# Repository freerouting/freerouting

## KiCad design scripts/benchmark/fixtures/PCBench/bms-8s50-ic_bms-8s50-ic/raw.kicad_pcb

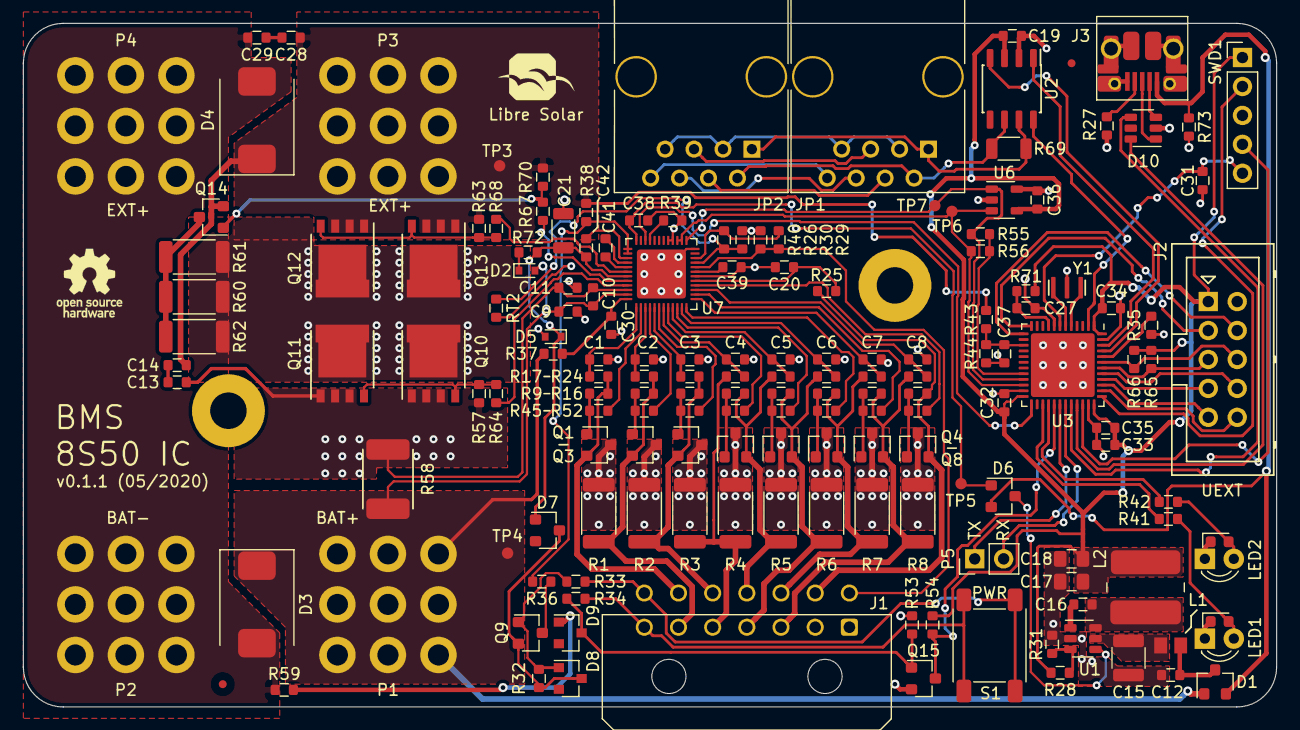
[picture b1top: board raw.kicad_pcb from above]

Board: 2 copper layers, 110.0 x 60.0 mm, 166 parts (0 on the bottom side), 125 nets.

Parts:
C1, C2, C3, C4, C5, C6, C7, C8, C20: 47n; C_0603_1608
C9, C11, C12, C39: 1u; C_0603_1608
C10: 10n; C_0603_1608
C13, C14, C16, C19, C27, C28, C29, C31, C32, C33, C34, C36, C38: 100n; C_0603_1608
C15: 4.7u; C_1210_3225
C17, C18: 10u; C_0805_2012
C21: 4.7u; C_1206_3216
C30: 470n; C_0603_1608
C35: 4.7u; C_0603_1608
C37, C41, C42: 4.7n; C_0603_1608
D1, D6, D7: BAV70; SOT-23
D2, D5: PMEG6002; D_SOD-523
D3, D4: SMCJ36A; D_SMC
D8, D9: 12V; D_SOT-23_ANK
D10: USBLC6-2SC6; SOT-23-6
H1, H2: MountingHole; MountingHole_3.2mm_M3_Pad
J1: Conn_01x10; Molex_Micro-Fit_3.0_43045-1400_2x07_P3.00mm_Horizontal
J2: UEXT; Box_Header_2x05x2.54mm_Straight
J3: USB_B_Micro; USB_Micro-B_10103594-0001LF
JP1, JP2: RJ45_NS; RJ45_8P8C
L1: 4.7uH; L_0805_2012Metric
L2: 47uH; Bourns_SRN6045TA
LED1, LED2: LED; LED_0603_D3.0mm
LOGO1: OPEN_HARDWARE; OSHW-Logo_5.7x6mm_SilkScreen
LOGO2: LIBRE_SOLAR; LIBRESOLAR_LOGO
P1, P2, P3, P4: CONN_01X01; Wuerth_WP-THRBU_74650195
P5: CONN_01X02; PinHeader_1x02_P2.54mm_Vertical
Q1, Q2, Q3, Q9: NDS0605; SOT-23
Q4, Q5, Q6, Q7, Q8, Q14, Q15: BSS138; SOT-23
Q10, Q11, Q12, Q13: BSC016N06NS; 5X6_MOSFET
R1, R2, R3, R4, R5, R6, R7, R8: 33; R_2010_5025
R9, R10, R11, R12, R13, R14, R15, R16, R27, R43, R73: 330k; R_0603_1608
R17, R18, R19, R20, R21, R22, R23, R24, R25, R36, R38, R41, R42, R54: 1k; R_0603_1608
R26, R30, R33, R34, R45, R46, R47, R48, R49, R50, R51, R52: 10k; R_0603_1608
R28: 50.5k; R_0603_1608
R29, R31, R40, R44: 22k; R_0603_1608
R32, R35, R53, R57, R63, R70: 1M; R_0603_1608
R37, R59, R64, R67, R68, R71: 100; R_0603_1608
R39, R55, R56, R65, R66: 2.2k; R_0603_1608
R58: 1m; R_Shunt_2512
R60, R61, R62: 330; R_2010_5025
R69: 120; R_1206_3216
R72: 4R7; R_0603_1608
RT2: 10k; R_0603_1608
S1: SW_PUSH; SW_SPST_6mm
SWD1: ST_Nucleo_SWD_5p; PinHeader_1x05_P2.54mm_Vertical
TP3: Ext+; TestPoint_1mm_pad
TP4: Bat+; TestPoint_1mm_pad
TP5: Regout; TestPoint_1mm_pad
TP6: SDA; TestPoint_1mm_pad
TP7: SCL; TestPoint_1mm_pad
U1: TPS560430X; SOT-23-6
U2: TCAN334; SOIC-8_3.9x4.9mm_Pitch1.27mm
U3: STM32F072CBU6; QFN-48-1EP_7x7mm_P0.5mm_EP5.6x5.6mm
U6: 24AA32; SOT-23-5
U7: ISL94202; QFN-48-1EP_6x6mm_P0.4mm_EP4.3x4.3mm
Y1: 8MHz; Resonator_Murata_CSTNE

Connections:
+3V3: C17.1, C18.1, C19.1, C32.1, C33.1, C34.1, C35.1, C36.1, J2.1, L2.2, R28.1, R54.2, R65.2, R66.2, R71.2, SWD1.1, U2.3, U3.1, U3.24, U3.36, U3.48, U6.4
+5V: D1.2, D6.2, J3.1, R73.1
/BAT+: C9.1, C10.1, D1.1, D2.2, D3.1, P1.1, R37.1, R58.2, TP4.1, U7.47
/BAT-: C29.2, D3.2, D4.2, P2.1, P4.1, R59.1
/CAN_V+: JP1.8, JP2.8
/EXT+: C14.2, C28.1, D4.1, P3.1, Q12.S, Q13.S, Q14.2, R38.1, R43.1, R63.1, R70.1, TP3.1
/ISL94202/ALERT: U3.25, U7.34
/ISL94202/BTN_1: J1.14, R33.1, S1.2
/ISL94202/BTN_2: J1.7, R34.2, S1.1
/ISL94202/BTN_SIGNAL: Q15.3, R54.1, U3.29
/ISL94202/CB1: R52.1, U7.16
/ISL94202/CB2: R51.1, U7.14
/ISL94202/CB3: R50.1, U7.12
/ISL94202/CB4: R49.1, U7.10
/ISL94202/CB5: R48.1, U7.8
/ISL94202/CB6: R47.1, U7.6
/ISL94202/CB7: R46.1, U7.4
/ISL94202/CB8: R45.1, U7.2
/ISL94202/CELL1+: J1.3, Q7.2, R8.2, R15.1, R24.2
/ISL94202/CELL1-: J1.9, Q8.2, R16.1, R25.2
/ISL94202/CELL2+: J1.10, Q6.2, R7.2, R14.1, R23.2
/ISL94202/CELL3+: J1.4, Q5.2, R6.2, R13.1, R22.2
/ISL94202/CELL4+: J1.11, Q4.2, R5.2, R12.1, R21.2
/ISL94202/CELL5+: J1.5, R3.1, R4.2, R20.2
/ISL94202/CELL6+: J1.12, Q3.2, R2.1, R11.2, R19.2
/ISL94202/CELL7+: J1.6, Q2.2, R1.1, R10.2, R18.2
/ISL94202/CELL8+: J1.13, Q1.2, R9.2, R17.2
/ISL94202/CFET: R64.2, U7.45
/ISL94202/CHG+: D5.2, Q10.D, Q11.D, Q12.D, Q13.D, R60.2, R61.2, R62.2
/ISL94202/CHMON: R36.1, R38.2, U7.37, U7.38
/ISL94202/CSI2: C10.2, C11.1, C13.1, Q10.S, Q11.S, R57.2, R58.1, U7.46
/ISL94202/DFET: R68.1, U7.42
/ISL94202/NTC_BAT: J1.8, R29.1, R30.2, U7.20
/ISL94202/PCFET: R67.2, U7.44
/ISL94202/RGO: C38.1, D6.1, TP5.1, U7.36
/ISL94202/TEMPO: R29.2, R40.2, U7.22
/ISL94202/VC0: C20.1, R25.1, U7.17
/ISL94202/VC1: C8.1, R24.1, U7.15
/ISL94202/VC2: C7.1, R23.1, U7.13
/ISL94202/VC3: C6.1, R22.1, U7.11
/ISL94202/VC4: C5.1, R21.1, U7.9
/ISL94202/VC5: C4.1, R20.1, U7.7
/ISL94202/VC6: C3.1, R19.1, U7.5
/ISL94202/VC7: C2.1, R18.1, U7.3
/ISL94202/VC8: C1.1, R17.1, U7.1
/ISL94202/VDD: C21.1, C42.1, D5.1, D7.1, R72.1, U7.43
/ISL94202/XT2: R26.2, R40.1, RT2.1, U7.21
/MCU/BOOT0: R35.2, U3.44
/MCU/CAN_H: JP1.1, JP2.1, R69.1, U2.7
/MCU/CAN_L: JP1.2, JP2.2, R69.2, U2.6
/MCU/CAN_RX: U2.4, U3.45
/MCU/CAN_STB: U2.8, U3.2
/MCU/CAN_TX: U2.1, U3.46
/MCU/I2C1_SCL: J2.5, R65.1, U3.42
/MCU/I2C1_SDA: J2.6, R66.1, U3.43
/MCU/I2C2_PULLUP: R55.2, R56.2, U3.20
/MCU/I2C2_SCL: R55.1, TP7.1, U3.21, U6.1, U7.25
/MCU/I2C2_SDA: R56.1, TP6.1, U3.22, U6.3, U7.26, U7.27
/MCU/LED1: R41.2, U3.27
/MCU/LED2: R42.2, U3.28
/MCU/SPI1_MISO: J2.7, U3.40
/MCU/SPI1_MOSI: J2.8, U3.41
/MCU/SPI1_SCK: J2.9, U3.39
/MCU/SSEL: J2.10, U3.38
/MCU/SWCLK: SWD1.2, U3.37
/MCU/SWDIO: SWD1.4, U3.34
/MCU/USART1_RX: P5.2, U3.31
/MCU/USART1_TX: P5.1, U3.30
/MCU/USART2_RX: J2.4, U3.13
/MCU/USART2_TX: J2.3, U3.12
/MCU/USB_D+: D10.1, J3.3
/MCU/USB_D-: D10.3, J3.2
/MCU/USB_DM: D10.4, U3.32
/MCU/USB_DP: D10.6, U3.33
/MCU/~RESET: C31.1, SWD1.5, U3.7
/Power Supply/EN: D6.3, U1.4
/Power Supply/FB: R28.2, R31.1, U1.3
/Power Supply/SW: C16.2, L2.1, U1.6
/Power Supply/VIN: C15.1, L1.2, U1.5
/V_EXT: C37.1, R43.2, R44.1, U3.15
GND: C1.2, C2.2, C3.2, C4.2, C5.2, C6.2, C7.2, C8.2, C9.2, C11.2, C12.2, C15.2, C17.2, C18.2, C19.2, C20.2, C21.2, C27.2, C30.2, C31.2, C32.2, C33.2, C34.2, C35.2, C36.2, C37.2, C38.2, C39.2, D9.2, D10.2, J1.1, J1.2, J2.2, J3.5, J3.6, JP1.3, JP1.7, JP2.3, JP2.7, LED1.1, LED2.1, Q15.2, R26.1, R27.2, R30.1, R31.2, R35.1, R39.2, R44.2, R53.1, R59.2, R73.2, RT2.2, SWD1.3, U1.2, U2.2, U3.8, U3.23, U3.35, U3.47, U3.49, U6.2, U6.5, U7.18, U7.24, U7.28, U7.29, U7.49, Y1.2
unnamed: C12.1, D1.3, L1.1
unnamed: C13.2, C14.1
unnamed: C16.1, U1.1
unnamed: C27.1, R71.1, U3.9
unnamed: C28.2, C29.1
unnamed: C30.1, R37.2, U7.48
unnamed: C39.1, U7.19
unnamed: C41.1, U7.41
unnamed: C41.2, U7.40
unnamed: C42.2, U7.39
unnamed: D2.1, R72.2
unnamed: D7.3, D8.1, Q9.2, R32.2
unnamed: D8.2, Q9.1, R32.1, R33.2
unnamed: D9.1, Q15.1, R34.1, R53.2
unnamed: J3.4, R27.1
unnamed: JP1.4, JP2.4
unnamed: JP1.5, JP2.5
unnamed: JP1.6, JP2.6
unnamed: LED1.2, R41.1
unnamed: LED2.2, R42.1
unnamed: Q1.1, R9.1, R45.2
unnamed: Q1.3, R1.2
unnamed: Q2.1, R10.1, R46.2
unnamed: Q2.3, R2.2
unnamed: Q3.1, R11.1, R47.2
unnamed: Q3.3, R3.2
unnamed: Q4.1, R12.2, R48.2
unnamed: Q4.3, R4.1
unnamed: Q5.1, R13.2, R49.2
unnamed: Q5.3, R5.1
unnamed: Q6.1, R14.2, R50.2
unnamed: Q6.3, R6.1
unnamed: Q7.1, R15.2, R51.2
unnamed: Q7.3, R7.1
unnamed: Q8.1, R16.2, R52.2
unnamed: Q8.3, R8.1
unnamed: Q9.3, R36.2
unnamed: Q10.G, Q11.G, R57.1, R64.1
unnamed: Q12.G, Q13.G, R63.2, R68.2
unnamed: Q14.1, R67.1, R70.2
unnamed: Q14.3, R60.1, R61.1, R62.1
unnamed: R39.1, U7.33
unnamed: U3.5, Y1.3
unnamed: U3.6, Y1.1

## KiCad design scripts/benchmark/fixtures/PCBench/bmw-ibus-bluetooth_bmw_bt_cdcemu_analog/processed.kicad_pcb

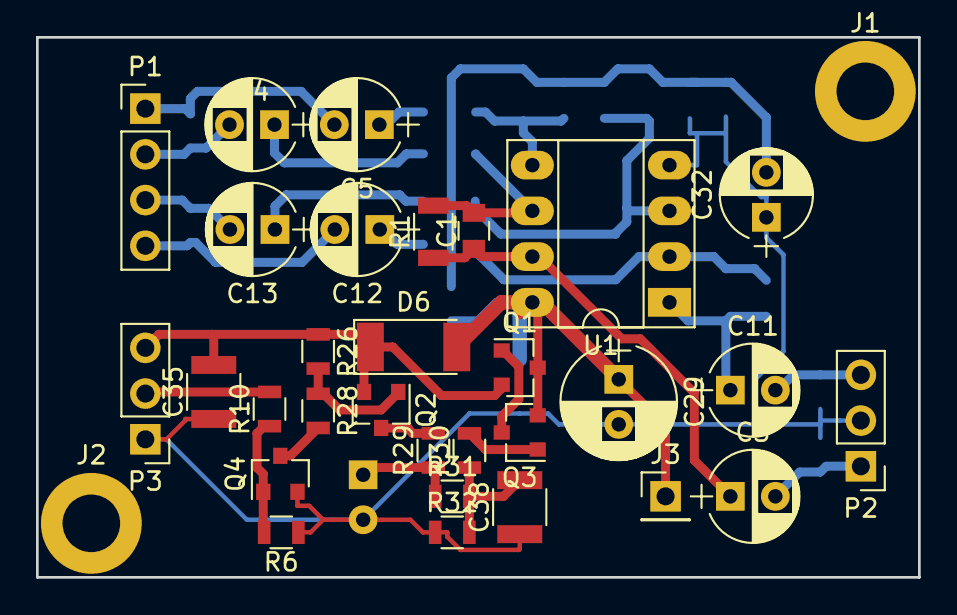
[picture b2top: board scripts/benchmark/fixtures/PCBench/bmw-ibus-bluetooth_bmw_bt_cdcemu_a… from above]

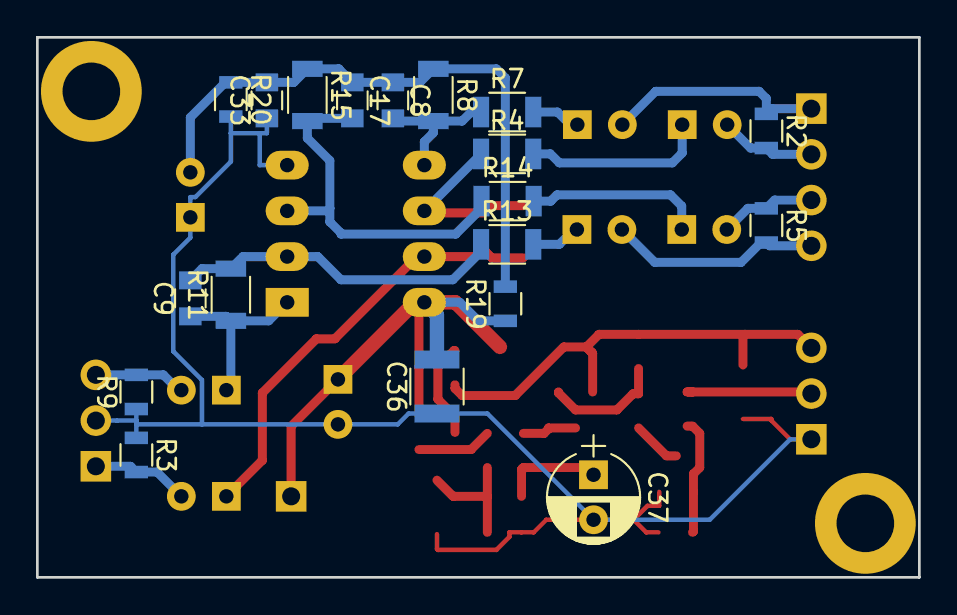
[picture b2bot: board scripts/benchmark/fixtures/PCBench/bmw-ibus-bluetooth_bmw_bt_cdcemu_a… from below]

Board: 2 copper layers, 49.0 x 30.0 mm, 51 parts (19 on the bottom side), 29 nets.

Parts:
C1, C8, C9, C17: 33p; C_0805
C3, C11: 10u; CP_Radial_D5.0mm_P2.50mm
C4, C5, C12, C13: 1u; CP_Radial_D5.0mm_P2.50mm
C29: 100u; CP_Radial_D6.3mm_P2.50mm
C32: 47u; CP_Radial_D5.0mm_P2.50mm
C33: 100n; C_0805
C35, C36, C38: 0.22u; C_1210
C37: 22u; CP_Radial_D5.0mm_P2.50mm
D6: D; D_MELF
J1, J2: Screw; MountingHole_3.2mm_M3_DIN965_Pad
J3: Mic Bias; Pin_Header_Straight_1x01_Pitch2.54mm
P1: DIFF_IN; Pin_Header_Straight_1x04_Pitch2.54mm
P2: AUD_OUT; Pin_Header_Straight_1x03_Pitch2.54mm
P3: PWR_EN; Pin_Header_Straight_1x03_Pitch2.54mm
Q1: BC807; SOT-23
Q2: 2N7002; SOT-23
Q3: B847; SOT-23
Q4: Q_NMOS_GSD; SOT-23
R1, R4, R7, R8, R11, R13, R14, R15: 10k; R_1206
R2, R5: 680; R_0805
R3, R6, R9, R26, R28, R31: 10k; R_0805
R10, R30: 1k; R_0805
R19, R20: 2.2k; R_0805
R29: 15k; R_0805
R32: 220k; R_0805
U1: NE5532; DIP-8_W7.62mm_Socket_LongPads

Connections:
+12P: C29.1, C36.2, D6.2, J3.1, Q1.3, Q3.2, R19.1, U1.8
/B+: C35.2, D6.1, P3.3, Q1.2, Q2.2, R26.1
/EN12: P3.2, R10.2
/L: C3.2, P2.1, R3.2
/R: C11.2, P2.3, R9.2
GNDA: C29.2, C32.1, C33.1, C35.1, C36.1, C37.2, C38.1, P2.2, P3.1, Q4.2, R3.1, R6.1, R9.1, R20.2, R32.1, U1.4
unnamed: C1.1, C3.1, R1.1, U1.7
unnamed: C1.2, R1.2, R4.1, U1.6
unnamed: C4.1, R4.2
unnamed: C5.1, R7.2
unnamed: C8.2, R7.1, R8.2, U1.5
unnamed: C9.2, R11.2, R13.1, U1.2
unnamed: C9.1, C11.1, R11.1, U1.1
unnamed: C12.1, R13.2
unnamed: C13.1, R14.2
unnamed: C17.2, R14.1, R15.2, U1.3
unnamed: C37.1, R29.1, R31.1
unnamed: C38.2, R30.1, R31.2, R32.2
unnamed: Q1.1, Q3.3
unnamed: Q2.1, R26.2, R28.1
unnamed: Q2.3, R29.2
unnamed: Q3.1, R30.2
unnamed: Q4.1, R6.2, R10.1
unnamed: Q4.3, R28.2
SPK_LN: C4.2, P1.2, R2.2
SPK_LP: C5.2, P1.1, R2.1
SPK_RN: C12.2, P1.4, R5.2
SPK_RP: C13.2, P1.3, R5.1
VGND: C8.1, C17.1, C32.2, C33.2, R8.1, R15.1, R19.2, R20.1

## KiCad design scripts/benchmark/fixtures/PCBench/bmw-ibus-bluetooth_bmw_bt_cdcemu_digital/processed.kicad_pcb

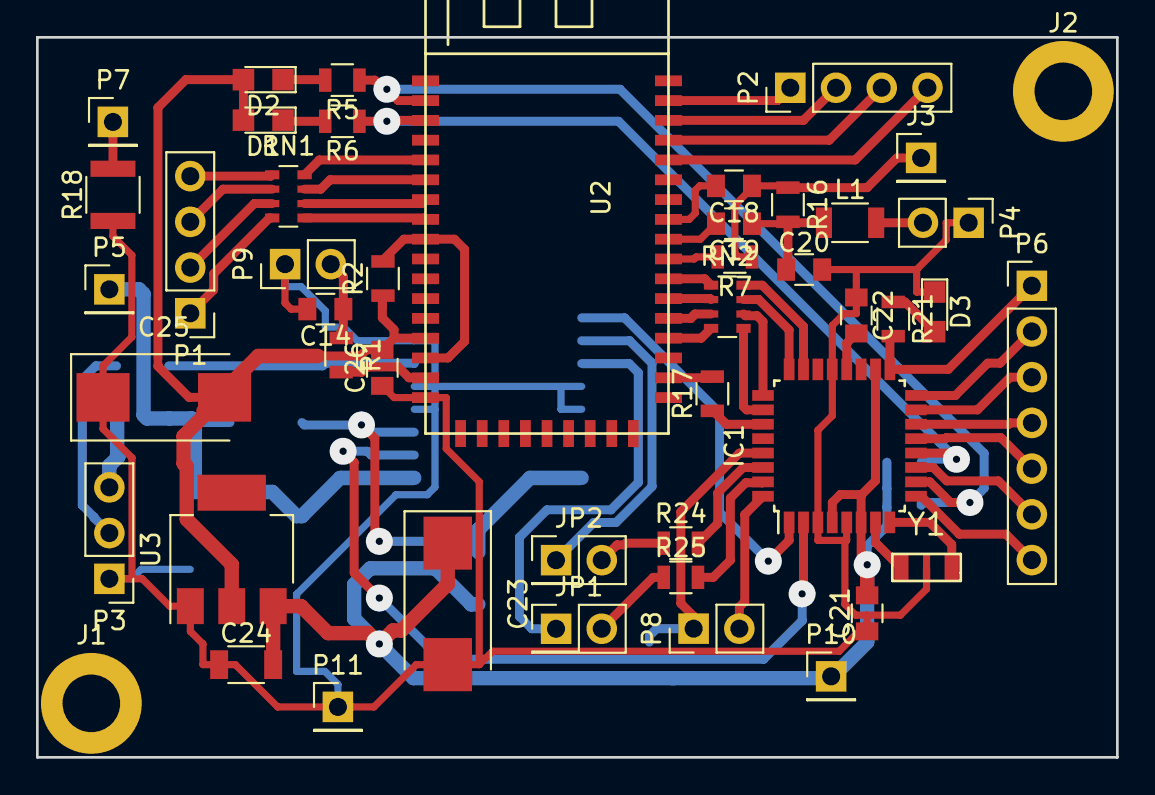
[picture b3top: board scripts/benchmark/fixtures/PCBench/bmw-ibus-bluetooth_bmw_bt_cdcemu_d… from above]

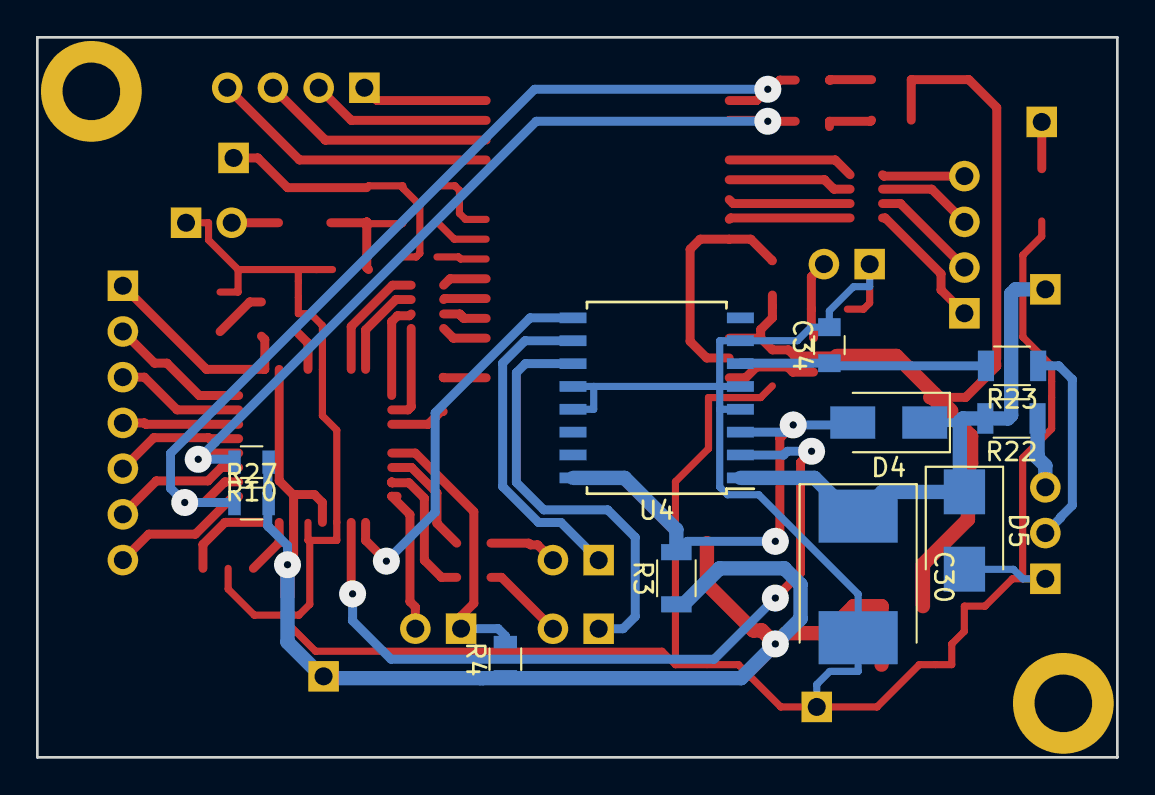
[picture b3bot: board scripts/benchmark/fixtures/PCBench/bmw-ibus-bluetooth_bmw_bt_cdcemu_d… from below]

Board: 2 copper layers, 60.0 x 40.0 mm, 58 parts (11 on the bottom side), 65 nets.

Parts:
C14, C18, C19, C22: 100n; C_0805
C20: 15p; C_0805
C21, C26: 0.22u; C_0805
C23, C25: 22u; CP_Tantalum_Case-D_EIA-7343-31_Wave
C24: 0.22u; C_1206
C30: 22u; CP_Tantalum_Case-E_EIA-7260-38_Wave
C34: 10p; C_0805
D1, D2, D3: LED; LED_0805
D4: D_Schottky; D_SMA
D5: 24v; D_SMB
IC1: ATMEGA328P-A; LQFP-32_7x7mm_Pitch0.8mm
J1, J2: Screw; MountingHole_3.2mm_M3_DIN965_Pad
J3: External Mic Bias; Pin_Header_Straight_1x01_Pitch2.54mm
JP1: Tx; Pin_Header_Straight_2x01_Pitch2.54mm
JP2: Rx; Pin_Header_Straight_2x01_Pitch2.54mm
L1: 15n; R_1206
P1: SPI PROG; Pin_Header_Straight_1x04_Pitch2.54mm
P2: CONN_01X04; Pin_Header_Straight_1x04_Pitch2.54mm
P3: CAR; Pin_Header_Straight_1x03_Pitch2.54mm
P4: MIC_A; Pin_Header_Straight_1x02_Pitch2.54mm
P5: B+; Pin_Header_Straight_1x01_Pitch2.54mm
P6: CONN_01X07; Pin_Header_Straight_1x07_Pitch2.54mm
P7: GNDA; Pin_Header_Straight_1x01_Pitch2.54mm
P8: CONN_01X02; Pin_Header_Straight_1x02_Pitch2.54mm
P9: 1v8; Pin_Header_Straight_1x02_Pitch2.54mm
P10: 5; Pin_Header_Straight_1x01_Pitch2.54mm
P11: GNDD; Pin_Header_Straight_1x01_Pitch2.54mm
R1, R4, R5, R6, R10, R16, R21, R27: 1k; R_0805
R2: 10k; R_0805
R3: 0; R_1206
R7: 0; R_0805
R17: 8.2k; R_0805
R18: 20; R_1210
R22, R23: 10; R_1206
R24, R25: 100; R_0805
RN1: 1k; R_Array_Convex_4x0603
RN2: 8.2k; R_Array_Convex_4x0603
U2: CSR8645
U3: LD1117S33CTR; SOT-223
U4: TH3122.4; SOIC-16W_7.5x10.3mm_Pitch1.27mm
Y1: 16MHz; SOIC-3

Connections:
+3V3: C25.2, C26.2, D1.2, D2.2, R2.1, U2.14, U3.2
+5V: C21.2, C23.1, C24.2, IC1.4, IC1.6, IC1.18, P10.1, R3.1, R4.1, R10.1, R27.2, U3.3
/B+: C30.1, D4.1, D5.1, P5.1, R22.2, U4.1
/EN: IC1.2, U4.2
/EN12: IC1.32, P8.2
/LED0: IC1.12, R6.1, R10.2, U2.3
/LED1: IC1.10, R5.1, R27.1, U2.2
/MIC_AN: C19.2, U2.35
/MIC_AP: C18.2, U2.36
/MIC_BIAS: C18.1, J3.1, R7.1, R16.1
/PB1: IC1.13, P6.5
/PB2: IC1.14, P6.4
/PB3-MOSI: IC1.15, P6.3
/PB4-MISO: IC1.16, P6.2
/PB5-SCK: IC1.17, P6.1, R21.2
/PC0: IC1.23, RN2.8
/PC1: IC1.24, RN2.7
/PC2: IC1.25, RN2.6
/PC3: IC1.26, RN2.5
/PC4: IC1.27, R17.1
/PD5: IC1.9, P6.7
/RESET: IC1.29, P8.1, R4.2
/RxD: IC1.30, R24.2
/SENSTA: IC1.1, U4.9
/SPK_LN: P2.2, U2.41
/SPK_LP: P2.1, U2.42
/SPK_RN: P2.4, U2.39
/SPK_RP: P2.3, U2.40
/TxD: IC1.31, R25.2
/TxDebug: IC1.11, P6.6
GNDD: C14.2, C20.2, C21.1, C22.1, C23.2, C24.1, C25.1, C26.1, C30.2, C34.2, D3.1, D5.2, IC1.3, IC1.5, IC1.21, P3.1, P4.1, P9.1, P11.1, R18.1, U2.17, U3.1, U4.4, U4.5, U4.7, U4.12, U4.13, Y1.2
unnamed: C14.1, P9.2, R1.1
unnamed: C19.1, C20.1, L1.1, R16.2
unnamed: C22.2, IC1.20
unnamed: C34.1, R23.2, U4.6
unnamed: D1.1, R6.2
unnamed: D2.1, R5.2
unnamed: D3.2, R21.1
unnamed: D4.2, R3.2, U4.3, U4.16
unnamed: IC1.7, Y1.3
unnamed: IC1.8, Y1.1
unnamed: JP1.1, U4.11
unnamed: JP1.2, R25.1
unnamed: JP2.1, U4.10
unnamed: JP2.2, R24.1
unnamed: L1.2, P4.2
unnamed: P1.1, RN1.4
unnamed: P1.2, RN1.3
unnamed: P1.3, RN1.2
unnamed: P1.4, RN1.1
unnamed: P3.2, R23.1
unnamed: P3.3, R22.1
unnamed: P7.1, R18.2
unnamed: R1.2, U2.16
unnamed: R2.2, U2.9, U2.15
unnamed: R7.2, U2.34
unnamed: R17.2, U2.28
unnamed: RN1.5, U2.8
unnamed: RN1.6, U2.7
unnamed: RN1.7, U2.6
unnamed: RN1.8, U2.5
unnamed: RN2.1, U2.33
unnamed: RN2.2, U2.32
unnamed: RN2.3, U2.31
unnamed: RN2.4, U2.30

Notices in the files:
scripts/benchmark/fixtures/PCBench/bms-8s50-ic_bms-8s50-ic/raw.kicad_pcb:
License: CC-BY-SA
